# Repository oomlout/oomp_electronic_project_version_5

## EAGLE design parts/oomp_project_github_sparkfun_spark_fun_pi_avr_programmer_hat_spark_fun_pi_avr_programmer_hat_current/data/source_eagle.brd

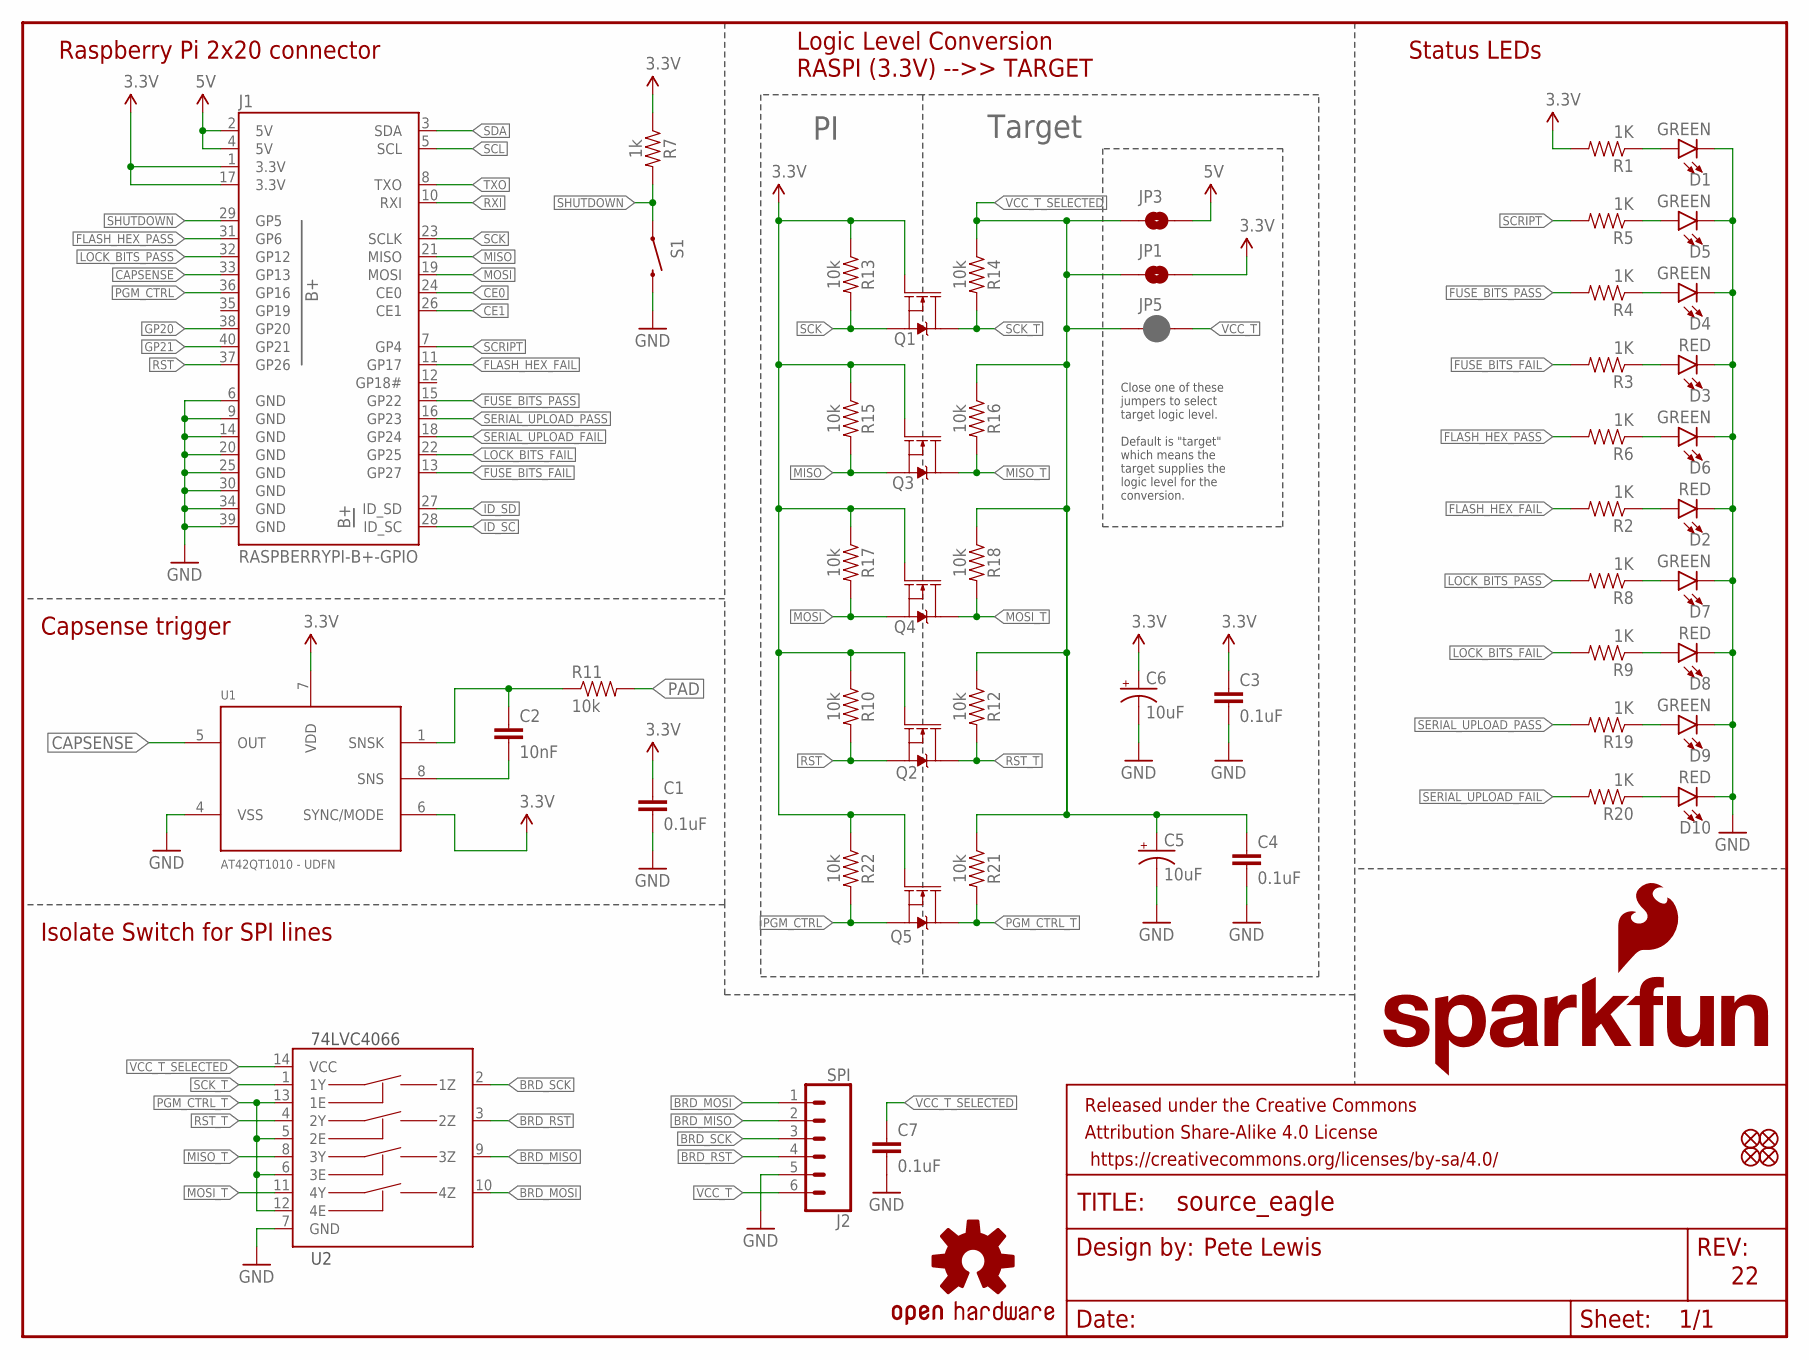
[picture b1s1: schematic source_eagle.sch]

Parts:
C1: 0.1uF; 0603-CAP
C2: 10nF; 0603-CAP
C3, C4, C7: 0.1uF; 0603
C5, C6: 10uF; EIA3216
D1, D4, D5, D6, D7, D9: GREEN; LED-1206
D2, D3, D8, D10: RED; LED-1206
FD1, FD2, FD3, FD4: FIDUCIALUFIDUCIAL; FIDUCIAL-MICRO
FRAME1: FRAME-LETTER; CREATIVE_COMMONS
J1: RASPBERRYPI-B+-GPIO; 2X20-SHROUDED
J2: SPI; 1X06-SMD_RA_MALE
JP1, JP3: JUMPER-SMT_2_NO_SILK; SMT-JUMPER_2_NO_SILK
JP5: JUMPER-SMT_2_NC_PASTE_SILK; SMT-JUMPER_2_NC_PASTE_SILK
LOGO1: SFE_LOGO_FLAME.2_INCH; SFE_LOGO_FLAME_.2
LOGO2: OSHW-LOGOL; OSHW-LOGO-L
LOGO3: SFE_LOGO_NAME.6_INCH; SFE_LOGO_NAME_.6
Q1, Q2, Q3, Q4, Q5: 220mA/50V/3.5Ω; SOT23-3
R1, R2, R3, R4, R5, R6, R8, R9, R19, R20: 1K; 0603-RES
R7: 1k; 0603
R10, R12, R13, R14, R15, R16, R17, R18, R21, R22: 10k; 0603
R11: 10k; 0603-RES
S1: SWITCH-MOMENTARY-2SMD; TACTILE-SWITCH-SMD
U1: AT42QT1010 - UDFN; UDFN/USON_8_PAD
U2: 74LVC4066; SO14

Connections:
3.3V: C1.1, C3.1, C6.+, J1.1 (3.3V), J1.17 (3.3V), JP1.2, Q1.1 (G), Q2.1 (G), Q3.1 (G), Q4.1 (G), Q5.1 (G), R1.2, R7.1, R10.1, R13.1, R15.1, R17.1, R22.1, U1.6 (SYNC/MODE), U1.7 (VDD)
5V: J1.2 (5V), J1.4 (5V), JP3.2
BRD_MISO: J2.2, U2.9 (3Z)
BRD_MOSI: J2.1, U2.10 (4Z)
BRD_RST: J2.4, U2.3 (2Z)
BRD_SCK: J2.3, U2.2 (1Z)
CAPSENSE: J1.33 (GP13), U1.5 (OUT)
CE0: J1.24 (CE0)
CE1: J1.26 (CE1)
FLASH_HEX_FAIL: J1.11 (GP17), R2.2
FLASH_HEX_PASS: J1.31 (GP6), R6.2
FUSE_BITS_FAIL: J1.13 (GP27), R3.2
FUSE_BITS_PASS: J1.15 (GP22), R4.2
GND: C1.2, C3.2, C4.2, C5.-, C6.-, C7.2, D1.C, D2.C, D3.C, D4.C, D5.C, D6.C, D7.C, D8.C, D9.C, D10.C, J1.6 (GND), J1.9 (GND), J1.14 (GND), J1.20 (GND), J1.25 (GND), J1.30 (GND), J1.34 (GND), J1.39 (GND), J2.5, S1.3 (2), U1.4 (VSS), U2.7 (GND)
GP20: J1.38 (GP20)
GP21: J1.40 (GP21)
ID_SC: J1.28 (ID_SC)
ID_SD: J1.27 (ID_SD)
LOCK_BITS_FAIL: J1.22 (GP25), R9.2
LOCK_BITS_PASS: J1.32 (GP12), R8.2
MISO: J1.21 (MISO), Q3.2 (S), R15.2
MISO_T: Q3.3 (D), R16.2, U2.8 (3Y)
MOSI: J1.19 (MOSI), Q4.2 (S), R17.2
MOSI_T: Q4.3 (D), R18.2, U2.11 (4Y)
unnamed: D6.A, R6.1
unnamed: D1.A, R1.1
unnamed: D2.A, R2.1
unnamed: D3.A, R3.1
unnamed: D7.A, R8.1
unnamed: D4.A, R4.1
unnamed: D5.A, R5.1
unnamed: D8.A, R9.1
unnamed: C2.2, U1.8 (SNS)
unnamed: C2.1, R11.1, U1.1 (SNSK)
unnamed: D9.A, R19.1
unnamed: D10.A, R20.1
PAD: R11.2
PGM_CTRL: J1.36 (GP16), Q5.2 (S), R22.2
PGM_CTRL_T: Q5.3 (D), R21.2, U2.5 (2E), U2.6 (3E), U2.12 (4E), U2.13 (1E)
RST: J1.37 (GP26), Q2.2 (S), R10.2
RST_T: Q2.3 (D), R12.2, U2.4 (2Y)
RXI: J1.10 (RXI)
SCK: J1.23 (SCLK), Q1.2 (S), R13.2
SCK_T: Q1.3 (D), R14.2, U2.1 (1Y)
SCL: J1.5 (SCL)
SCRIPT: J1.7 (GP4), R5.2
SDA: J1.3 (SDA)
SERIAL_UPLOAD_FAIL: J1.18 (GP24), R20.2
SERIAL_UPLOAD_PASS: J1.16 (GP23), R19.2
SHUTDOWN: J1.29 (GP5), R7.2, S1.1
TXO: J1.8 (TXO)
VCC_T: J2.6, JP5.2
VCC_T_SELECTED: C4.1, C5.+, C7.1, JP1.1, JP3.1, JP5.1, R12.1, R14.1, R16.1, R18.1, R21.1, U2.14 (VCC)

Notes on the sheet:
Raspberry Pi 2x20 connector
Pete Lewis
Status LEDs
Capsense trigger
Target
Logic Level Conversion RASPI (3.3V) -->> TARGET
Isolate Switch for SPI lines
Close one of these jumpers to select target logic level. Default is "target" which means the target supplies the logic level for the conversion.

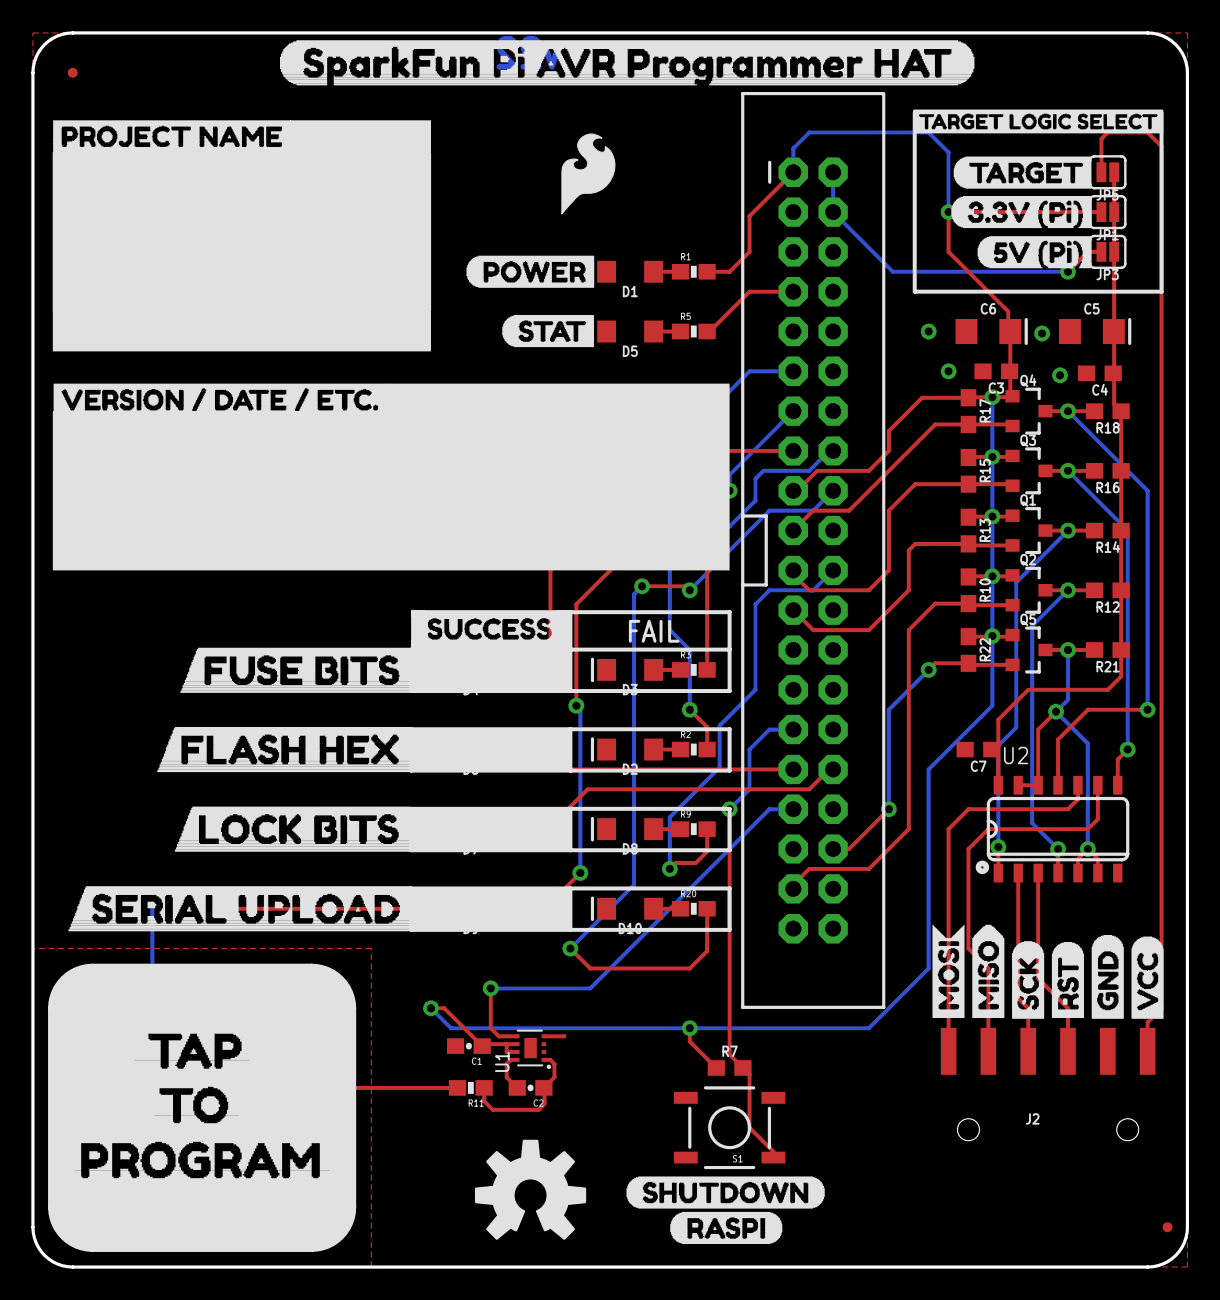
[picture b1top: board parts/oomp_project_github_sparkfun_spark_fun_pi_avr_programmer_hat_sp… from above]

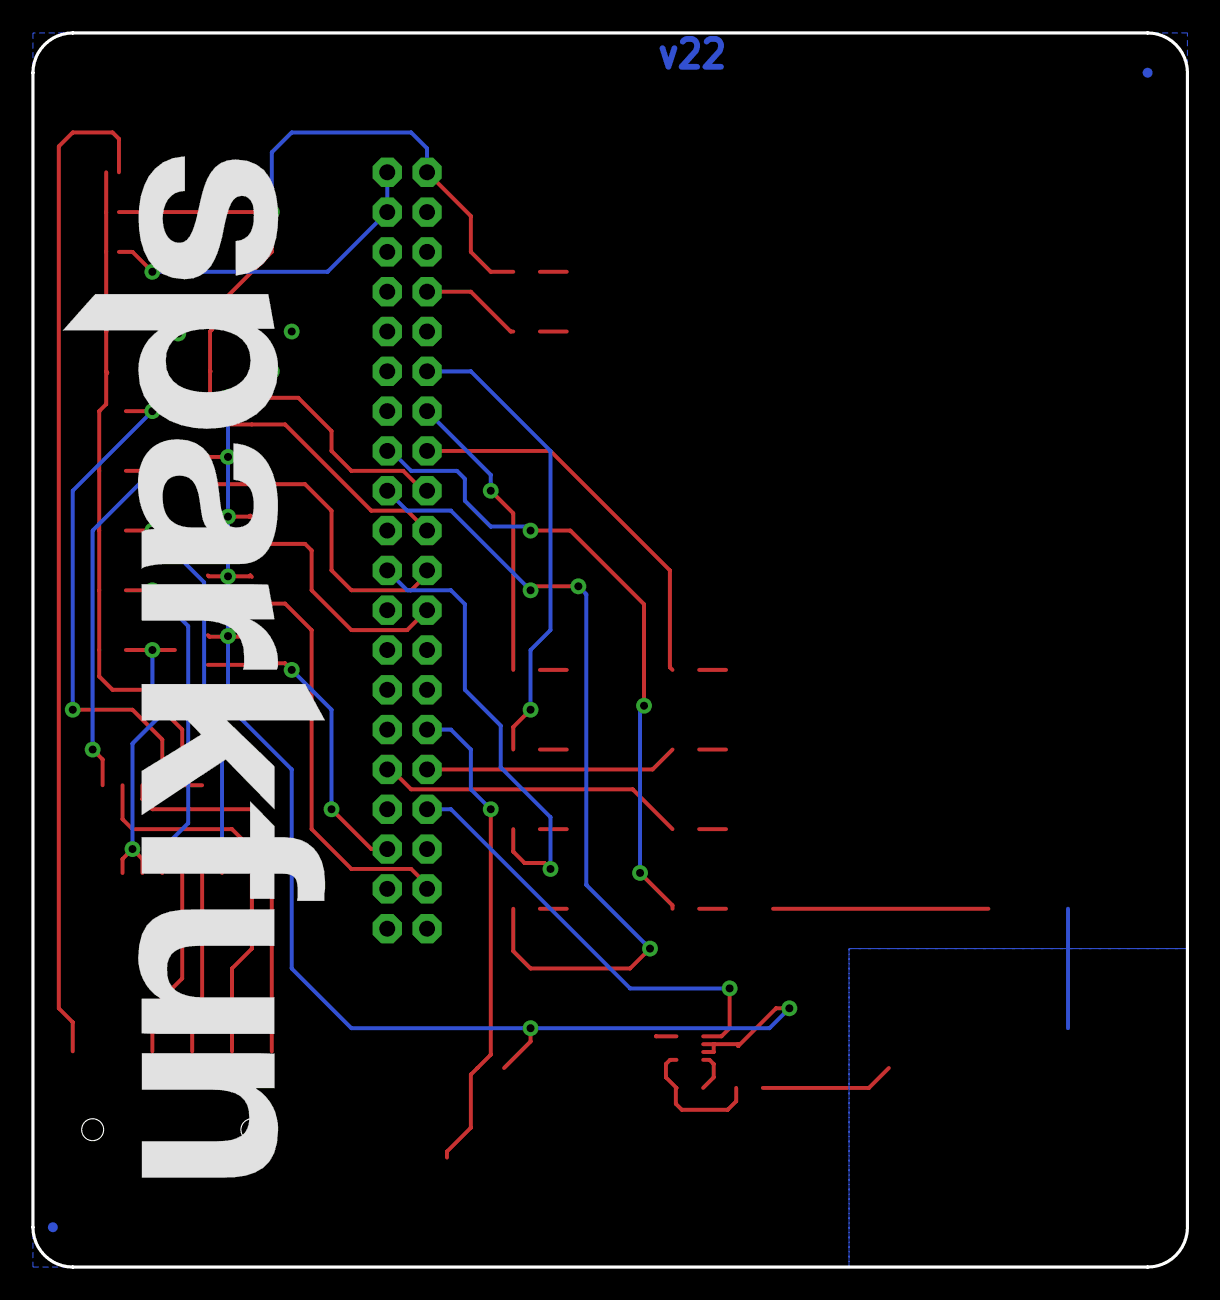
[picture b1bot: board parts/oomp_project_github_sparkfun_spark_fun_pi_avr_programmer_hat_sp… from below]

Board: 2 copper layers, 73.7 x 78.7 mm, 85 parts (3 on the bottom side), 42 nets.

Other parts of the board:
U$1: SPARKFUN_PI_AVR_PROGRAMMER_HAT0
U$2: PROJECT_NAME0
U$3: VERSION_#_DATE_#_ETC#0
U$4: TARGET_LOGIC_SELECT4
U$5: POWER0
U$6: STAT1
U$7: SHUTDOWN2
U$8: RASPI3
U$9: 3#3V_#PI#7
U$10: 5V_#PI#8
U$11: TARGET0
U$12: MISO1
U$13: MOSI0
U$14: SCK2
U$15: RST3
U$16: GND4
U$18: TAP0
U$19: TO1
U$20: PROGRAM2
U$21: VCC0
U$22: SUCCESS0
U$23: FUSE_BITS2
U$24: FLASH_HEX3
U$25: LOCK_BITS4
U$26: SERIAL_UPLOAD5

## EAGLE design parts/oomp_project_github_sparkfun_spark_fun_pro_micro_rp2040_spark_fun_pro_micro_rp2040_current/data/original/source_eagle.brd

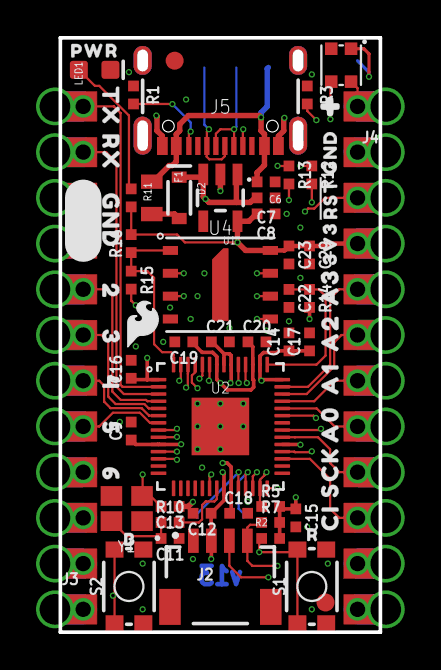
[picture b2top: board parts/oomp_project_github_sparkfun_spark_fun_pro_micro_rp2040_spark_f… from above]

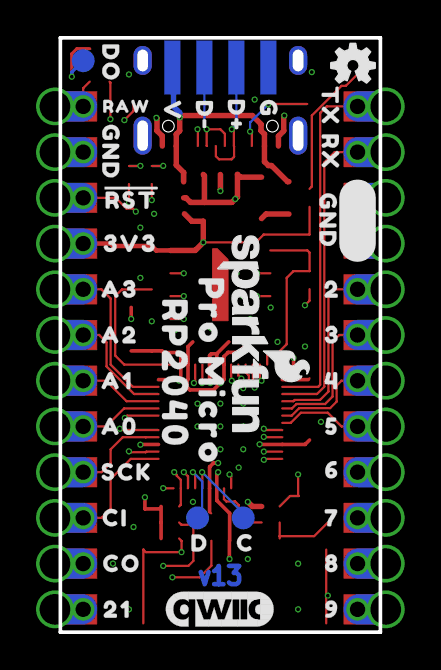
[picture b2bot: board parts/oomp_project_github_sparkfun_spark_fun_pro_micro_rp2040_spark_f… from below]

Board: 4 copper layers, 17.8 x 33.0 mm, 109 parts (39 on the bottom side), 49 nets.

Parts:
C6: 1.0uF; 0402-TIGHT
C7, C8: 10uF; 0402-TIGHT
C9, C12, C14, C15, C16, C17, C18, C19, C29: 0.1uF; 0402-TIGHT
C11, C13: 15pF; 0402-TIGHT
C20, C21, C22, C23: 2.2uF; 0402-TIGHT
D2: 3A/10V/280mV; SOD-323
F1: 6V 0.5A; 0805
FRAME2: FRAME-LEDGER; CREATIVE_COMMONS
J2: Qwiic; JST04_1MM_RA
J3, J4: 1X12_CASTELLATED
J5: USB Female Type C Connector; USB-C-16P_4LAYER-PADS
JP1, JP2: FIDUCIAL1X2; FIDUCIAL-1X2
JP14: USB_SOLDER_PADS; USB-SOLDER-PADS
LED1: RED; LED-0603
LOGO1: SFE_LOGO_NAME_FLAME.1_INCH; SFE_LOGO_NAME_FLAME_.1
LOGO3: QWIIC_LOGO_6MM; QWIIC_6MM
LOGO4: SFE_LOGO_FLAME.1_INCH; SFE_LOGO_FLAME_.1
LOGO5: SPECIAL_INSTRUCTIONS-ORDERING; ORDERING_INSTRUCTIONS
R1, R3: 5.1k; 0402-TIGHT
R2, R16: 10k; 0402-TIGHT
R5, R7: 2.2k; 0402-TIGHT
R10, R11, R15: 1k; 0402-TIGHT
R12, R13: 27; 0402-TIGHT
R14: 200; 0402-TIGHT
S1: Reset; TACTILE_SWITCH_SMD_4.6X2.8MM
S2: Boot; TACTILE_SWITCH_SMD_4.6X2.8MM
TP1, TP2, TP3: PAD.03X.05
U1: 3.3V; SOT23-5
U2: RP2040; QFN-56
U3: WS2812-2020
U4: W25QXX128MBIT; WSON-8-6X5-SKINNY_CENTERPAD
U$1, U$11: A00
U$2: GND_0
U$3: OSHW-LOGOMINI; OSHW-LOGO-MINI
U$4: PRO_MICRO0
U$5: #0
U$6: 70
U$7: 81
U$8: 92
U$9, U$64: CI4
U$10, U$67: SCK3
U$12, U$20: A10
U$13, U$33: A21
U$14, U$39: A32
U$15, U$22, U$74: GND2
U$16: 3V3_0
U$17: RAW0
U$18: C0
U$19, U$76: TX0
U$21, U$75: RX1
U$23, U$53: 20
U$24, U$54: 31
U$25, U$55: 42
U$26, U$56: 53
U$27, U$57: 64
U$28: D#1
U$29: D#2
U$30: G0
U$31: V3
U$32: 210
U$34: #RST#0
U$35: D1
U$36: B0
U$37: R0
U$38: RP20401
U$40: DO0
U$66: CO5
U$68: #RST#1
U$69: 3V30
U$73: PWR0
Y1: 12MHz; CRYSTAL-SMD-2X2.5MM

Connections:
0/TX0: J3.12, J3.12B, U2.2
1.1V: C18.1, C19.1, C20.1, U2.23, U2.45, U2.50
1/RX0: J3.11, J3.11B, U2.3
2: J3.8, J3.8B, U2.4
3: J3.7, J3.7B, U2.5
3.3V: C8.2, C9.1, C12.1, C14.1, C15.1, C16.1, C17.1, C21.1, C23.1, C29.1, J2.2, J4.4, J4.4B, R2.2, R5.2, R7.2, R11.2, R14.2, R16.2, U1.5, U2.1, U2.10, U2.22, U2.33, U2.42, U2.44, U2.48, U2.49, U4.8
4: J3.6, J3.6B, U2.6
5: J3.5, J3.5B, U2.7
6: J3.4, J3.4B, U2.8
7: J3.3, J3.3B, U2.9
8/TX1: J3.2, J3.2B, U2.11
9/RX1: J3.1, J3.1B, U2.12
16/SDA: J2.3, R5.1, U2.27
17/SCL: J2.4, R7.1, U2.28
20/SPI_CIPO: J4.10, J4.10B, U2.31
21/SPI_!CS!: J4.12, J4.12B, U2.32
22/SPI_SCK: J4.9, J4.9B, U2.34
23/SPI_COPI: J4.11, J4.11B, U2.35
25/WS2812-DI: U2.37, U3.3
!RESET!: J4.3, J4.3B, R2.1, S1.3, S1.4, U2.26
A0: J4.8, J4.8B, U2.38
A1: J4.7, J4.7B, U2.39
A2: J4.6, J4.6B, U2.40
A3: J4.5, J4.5B, U2.41
ADC_VDD: C22.1, R14.1, U2.43
BOOT: R15.2, S2.3, S2.4
GND: C6.1, C7.1, C8.1, C9.2, C11.1, C12.2, C13.1, C14.2, C15.2, C16.2, C17.2, C18.2, C19.2, C20.2, C21.2, C22.2, C23.2, C29.2, J2.1, J3.9, J3.9B, J3.10, J3.10B, J4.2, J4.2B, J5.GND, J5.GND2, JP14.GND, LED1.C, R1.1, R3.1, S1.1, S1.2, S2.1, S2.2, U1.2, U2.19, U2.EPAD, U3.2, U4.4
unnamed: TP3.P$1, U3.1
unnamed: J5.A5, R3.2
unnamed: J5.B5, R1.2
unnamed: LED1.A, R11.1
QSPI-0: U2.53, U4.5
QSPI-1: U2.55, U4.2
QSPI-2: U2.54, U4.3
QSPI-3: U2.51, U4.7
QSPI-CLK: U2.52, U4.6
QSPI-CS: R15.1, R16.1, U2.56, U4.1
RAW: C7.2, D2.C, J4.1, J4.1B, U1.1, U1.3, U3.4
RP_D1+: R13.2, U2.47
RP_D1-: R12.2, U2.46
RP_D+: J5.A6, J5.B6, JP14.D+, R13.1
RP_D-: J5.A7, J5.B7, JP14.D-, R12.1
SWDCK: TP1.P$1, U2.24
SWDIO: TP2.P$1, U2.25
USB_RAW: D2.A, F1.2
V_USB: C6.2, F1.1, J5.VBUS1, J5.VBUS2, JP14.VBUS
X1A: R10.2, U2.21
X1B: C11.2, R10.1, Y1.P1
X2: C13.2, U2.20, Y1.P3

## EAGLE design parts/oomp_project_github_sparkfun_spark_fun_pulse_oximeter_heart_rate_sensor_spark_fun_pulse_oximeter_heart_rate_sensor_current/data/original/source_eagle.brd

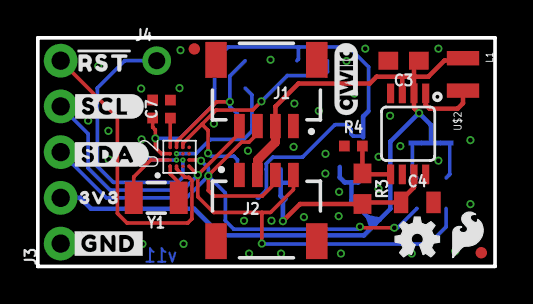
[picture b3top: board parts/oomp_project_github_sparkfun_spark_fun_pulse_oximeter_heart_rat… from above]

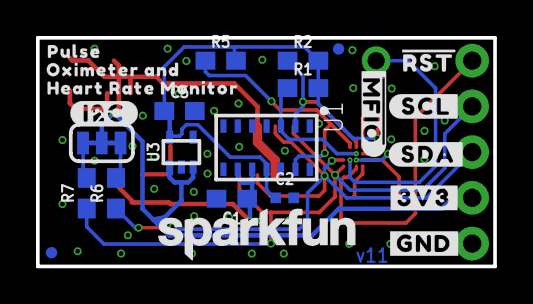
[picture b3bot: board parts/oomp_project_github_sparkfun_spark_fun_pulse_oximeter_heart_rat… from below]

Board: 2 copper layers, 25.4 x 12.7 mm, 50 parts (24 on the bottom side), 18 nets.

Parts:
C1, C3: 10uF; 0603
C2: 0.1uF; 0402-TIGHT
C4: 22uF; 0805
C5: 1.0uF; 0603
C6, C7: 1.0uF; 0402-TIGHT
FD1, FD2, FD3, FD4: FIDUCIALUFIDUCIAL; FIDUCIAL-MICRO
FRAME1: FRAME-LETTER; CREATIVE_COMMONS
I2C: JUMPER-SMT_3_2-NC_TRACE_SILK; SMT-JUMPER_3_2-NC_TRACE_SILK
J1, J2: QWIIC_RIGHT_ANGLE; JST04_1MM_RA
J3: 1X05_NO_SILK
J4: 1X01_NO_SILK
L1: 2.2μH; 0806
LOGO1: SFE_LOGO_FLAME.1_INCH; SFE_LOGO_FLAME_.1
LOGO2: OSHW-LOGOMINI; OSHW-LOGO-MINI
LOGO3: SFE_LOGO_NAME.1_INCH; SFE_LOGO_NAME_.1
LOGO4: SPECIAL_INSTRUCTIONS-ORDERING; ORDERING_INSTRUCTIONS
LOGO5: QWIIC_LOGO_4MM; QWIIC_4MM
R1, R2, R5, R6, R7: 4.7k; 0603
R3: 750K; 0603
R4: 100k; 0402-TIGHT
U1: MAX30101EFD; 14_PIN_OESIP
U2: MAX32664GWEA; 16_PIN_WLP
U3: 1.8V/100mA; SC70
U$1: #I2C#1348
U$2: PAM2401; MSOP8
U$3, U$5: #GND#0
U$4: #SCL#7
U$6, U$12: #RST#32
U$7: 3V338
U$8: #SDA#10
U$9: #3V3#1
U$10: #SDA#9
U$11: #SCL#9
U$13: ##MFIO##12
U$17: PULSE35
U$20: OXIMETER_AND36
U$21: HEART_RATE_MONITOR37
Y1: 32.768kHz; CRYSTAL-SMD-3.2X1.5MM

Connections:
1.8V: C2.1, C5.1, C6.1, R1.2, R2.2, R5.2, U1.P11, U2.3, U3.5
3.3V: C3.1, I2C.2, J1.2, J2.2, J3.2, L1.1, U3.1, U3.3, U$2.2, U$2.3
5V: C1.1, C4.1, R3.2, U1.P9, U1.P10, U$2.7
!HR_INT: R5.1, U1.P13, U2.6
!MFIO: J4.1, U2.16
!RST: J3.5, U2.12
GND: C1.2, C2.2, C3.2, C4.2, C5.2, C6.2, C7.2, J1.1, J2.1, J3.1, R4.1, U1.P4, U1.P12, U2.13, U3.2, U$2.4, U$2.8
HOST_SCL: J1.4, J2.4, J3.4, R7.1, U2.10
HOST_SDA: J1.3, J2.3, J3.3, R6.1, U2.9
unnamed: C7.1, U2.4
unnamed: R3.1, R4.2, U$2.5
unnamed: L1.2, U$2.1
unnamed: I2C.3, R6.2
unnamed: I2C.1, R7.2
unnamed: U2.1, Y1.P$1
unnamed: U2.2, Y1.P$2
SNSR_SCL: R2.1, U1.P2, U2.5
SNSR_SDA: R1.1, U1.P3, U2.14

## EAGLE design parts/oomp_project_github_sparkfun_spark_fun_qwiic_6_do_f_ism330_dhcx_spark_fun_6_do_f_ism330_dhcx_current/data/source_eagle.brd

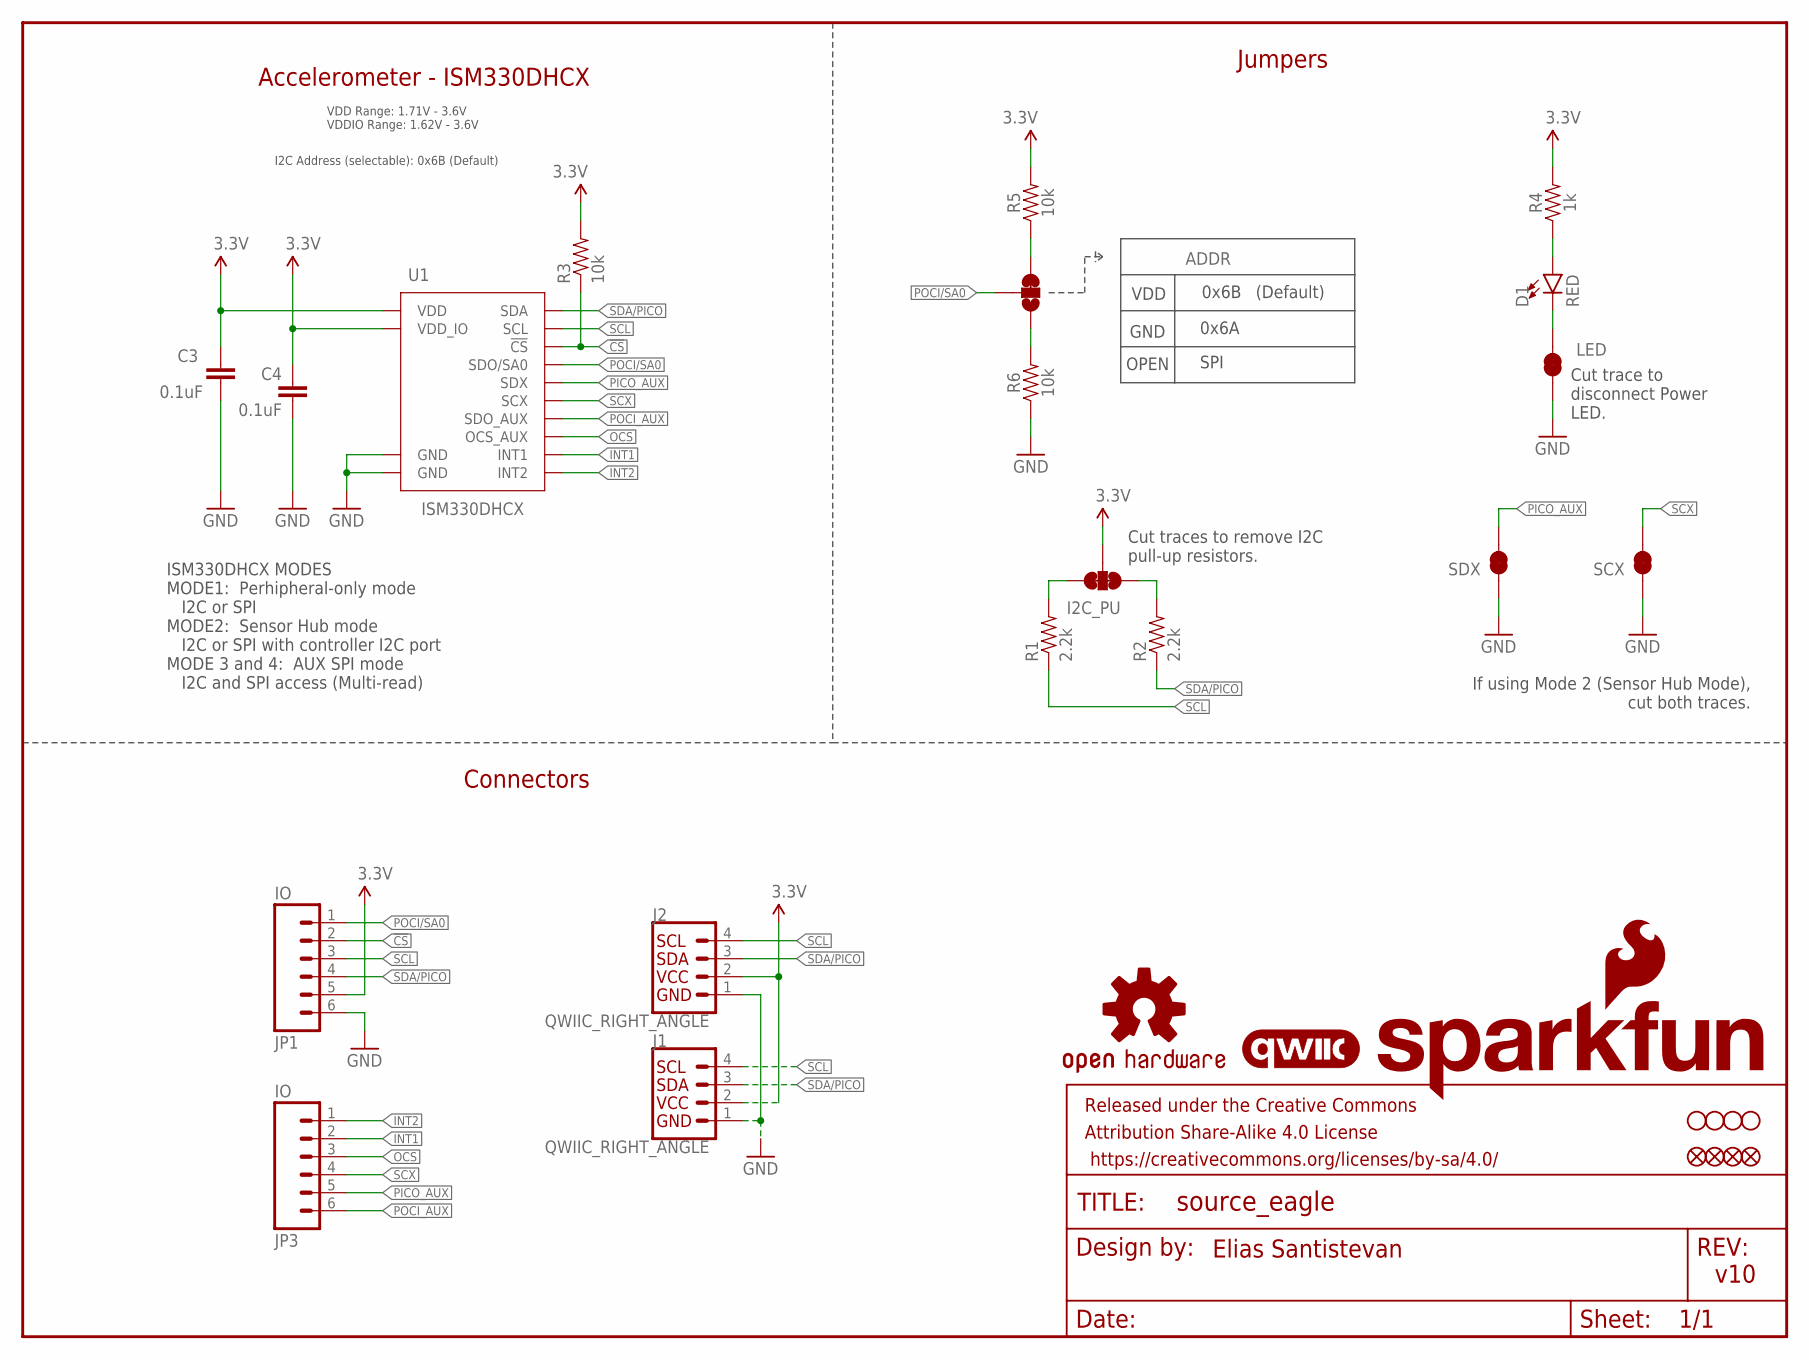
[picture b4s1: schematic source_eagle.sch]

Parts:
ADDR: JUMPER-SMT_3_1-NC_TRACE_SILK; SMT-JUMPER_3_1-NC_TRACE_SILK
C3, C4: 0.1uF; 0603
D1: RED; LED-0603
FD1, FD2: FIDUCIALUFIDUCIAL; FIDUCIAL-MICRO
FID1, FID2: FIDUCIALUFIDUCIAL; FIDUCIAL-MICRO
FRAME1: FRAME-LETTER; CREATIVE_COMMONS
I2C_PU: S_MODE; SMT-JUMPER_3_2-NC_TRACE_SILK
J1, J2: QWIIC_RIGHT_ANGLE; JST04_1MM_RA
JP1, JP3: IO; 1X06_NO_SILK
LED: JUMPER-SMT_2_NC_TRACE_SILK; SMT-JUMPER_2_NC_TRACE_SILK
LOGO1: QWIIC_LOGO_4MM; QWIIC_4MM
LOGO2: OSHW-LOGOMINI; OSHW-LOGO-MINI
LOGO3: SFE_LOGO_NAME_FLAME.1_INCH; SFE_LOGO_NAME_FLAME_.1
R1, R2: 2.2k; 0603
R3, R5, R6: 10k; 0603
R4: 1k; 0603
SCX: JUMPER-SMT_2_NC_TRACE_SILK; SMT-JUMPER_2_NC_TRACE_SILK
SDX: JUMPER-SMT_2_NC_TRACE_SILK; SMT-JUMPER_2_NC_TRACE_SILK
STANDOFF1, STANDOFF2, STANDOFF3, STANDOFF4: STAND-OFFTIGHT; STAND-OFF-TIGHT
U1: ISM330DHCX; LGA-14L

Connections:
3.3V: C3.1, C4.1, I2C_PU.2, J1.2, J2.2, JP1.5, R3.2, R4.2, R5.2, U1.P5 (VDD_IO), U1.P8 (VDD)
!CS!: JP1.2, R3.1, U1.P12 (!CS!)
GND: C3.2, C4.2, J1.1, J2.1, JP1.6, LED.1, R6.1, SCX.1, SDX.1, U1.P6 (GND), U1.P7 (GND)
INT1: JP3.2, U1.P4 (INT1)
INT2: JP3.1, U1.P9 (INT2)
unnamed: ADDR.3, R5.1
unnamed: D1.A, R4.1
unnamed: D1.C, LED.2
unnamed: I2C_PU.1, R1.2
unnamed: I2C_PU.3, R2.2
unnamed: ADDR.1, R6.2
OCS: JP3.3, U1.P10 (OCS_AUX)
PICO_AUX: JP3.5, SDX.2, U1.P2 (SDX)
POCI/SA0: ADDR.2, JP1.1, U1.P1 (SDO/SA0)
POCI_AUX: JP3.6, U1.P11 (SDO_AUX)
SCL: J1.4, J2.4, JP1.3, R1.1, U1.P13 (SCL)
SCX: JP3.4, SCX.2, U1.P3 (SCX)
SDA/PICO: J1.3, J2.3, JP1.4, R2.1, U1.P14 (SDA)

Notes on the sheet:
Accelerometer - ISM330DHCX
If using Mode 2 (Sensor Hub Mode), cut both traces.
Cut traces to remove I2C pull-up resistors.
ISM330DHCX MODES MODE1: Perhipheral-only mode I2C or SPI MODE2: Sensor Hub mode I2C or SPI with controller I2C port MODE 3 and 4: AUX SPI mode I2C and SPI access (Multi-read)
VDD Range: 1.71V - 3.6V VDDIO Range: 1.62V - 3.6V
v10
Jumpers
Cut trace to disconnect Power LED.
Connectors
VDD
GND
OPEN
0x6B
0x6A
SPI
Elias Santistevan
(Default)
I2C Address (selectable): 0x6B (Default)

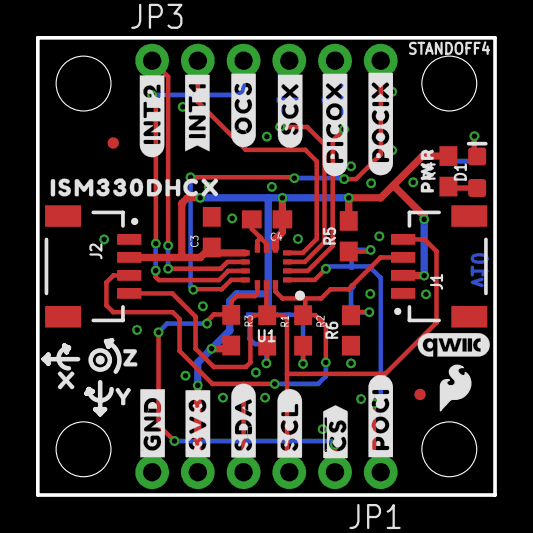
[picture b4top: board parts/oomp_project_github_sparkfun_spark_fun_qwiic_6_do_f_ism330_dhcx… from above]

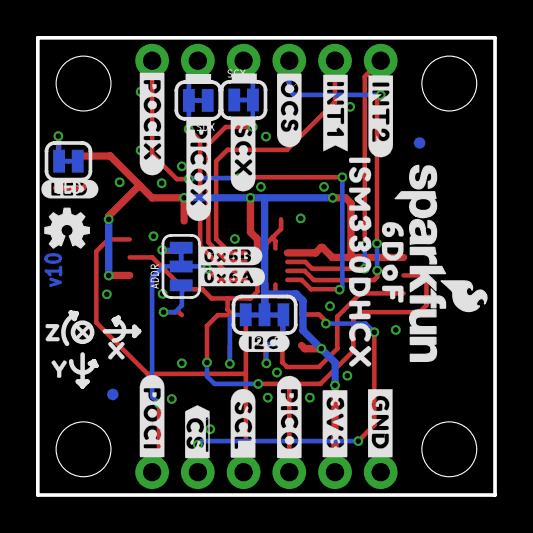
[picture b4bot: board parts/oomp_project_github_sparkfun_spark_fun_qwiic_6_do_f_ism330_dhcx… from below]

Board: 2 copper layers, 25.4 x 25.4 mm, 70 parts (30 on the bottom side), 18 nets.

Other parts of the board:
U$1, U$15: #3V3#1
U$2, U$17: #GND#0
U$3: ##CS##7
U$4: #SDA#4
U$5, U$22: #SCL#5
U$6: #POCI#11
U$7, U$19: #INT1#9
U$8: #INT2#2
U$9: #OCS#8
U$10: #SCX#9
U$11: #PICOX#10
U$12: ISM330DHCX331
U$13: #0X6A#11
U$14: #0X6B#11
U$16: #LED#11
U$18: #POCI#12
U$20: #OCS#7
U$23: #SCX#8
U$24: #POCIX#8
U$25: #I2C#11
U$26: #PICO#13
U$27: ##CS##8
U$28: PWR8
U$29: SFE_LOGO_FLAME_.1
U$30: ISM330DHCX20
U$31: 6DOF12
U$32: #PICOX#9
U$33: #POCIX#7
U$34, U$37: X2114
U$35, U$38: Y2115
U$36, U$39: Z2116
U$40: #INT2#3

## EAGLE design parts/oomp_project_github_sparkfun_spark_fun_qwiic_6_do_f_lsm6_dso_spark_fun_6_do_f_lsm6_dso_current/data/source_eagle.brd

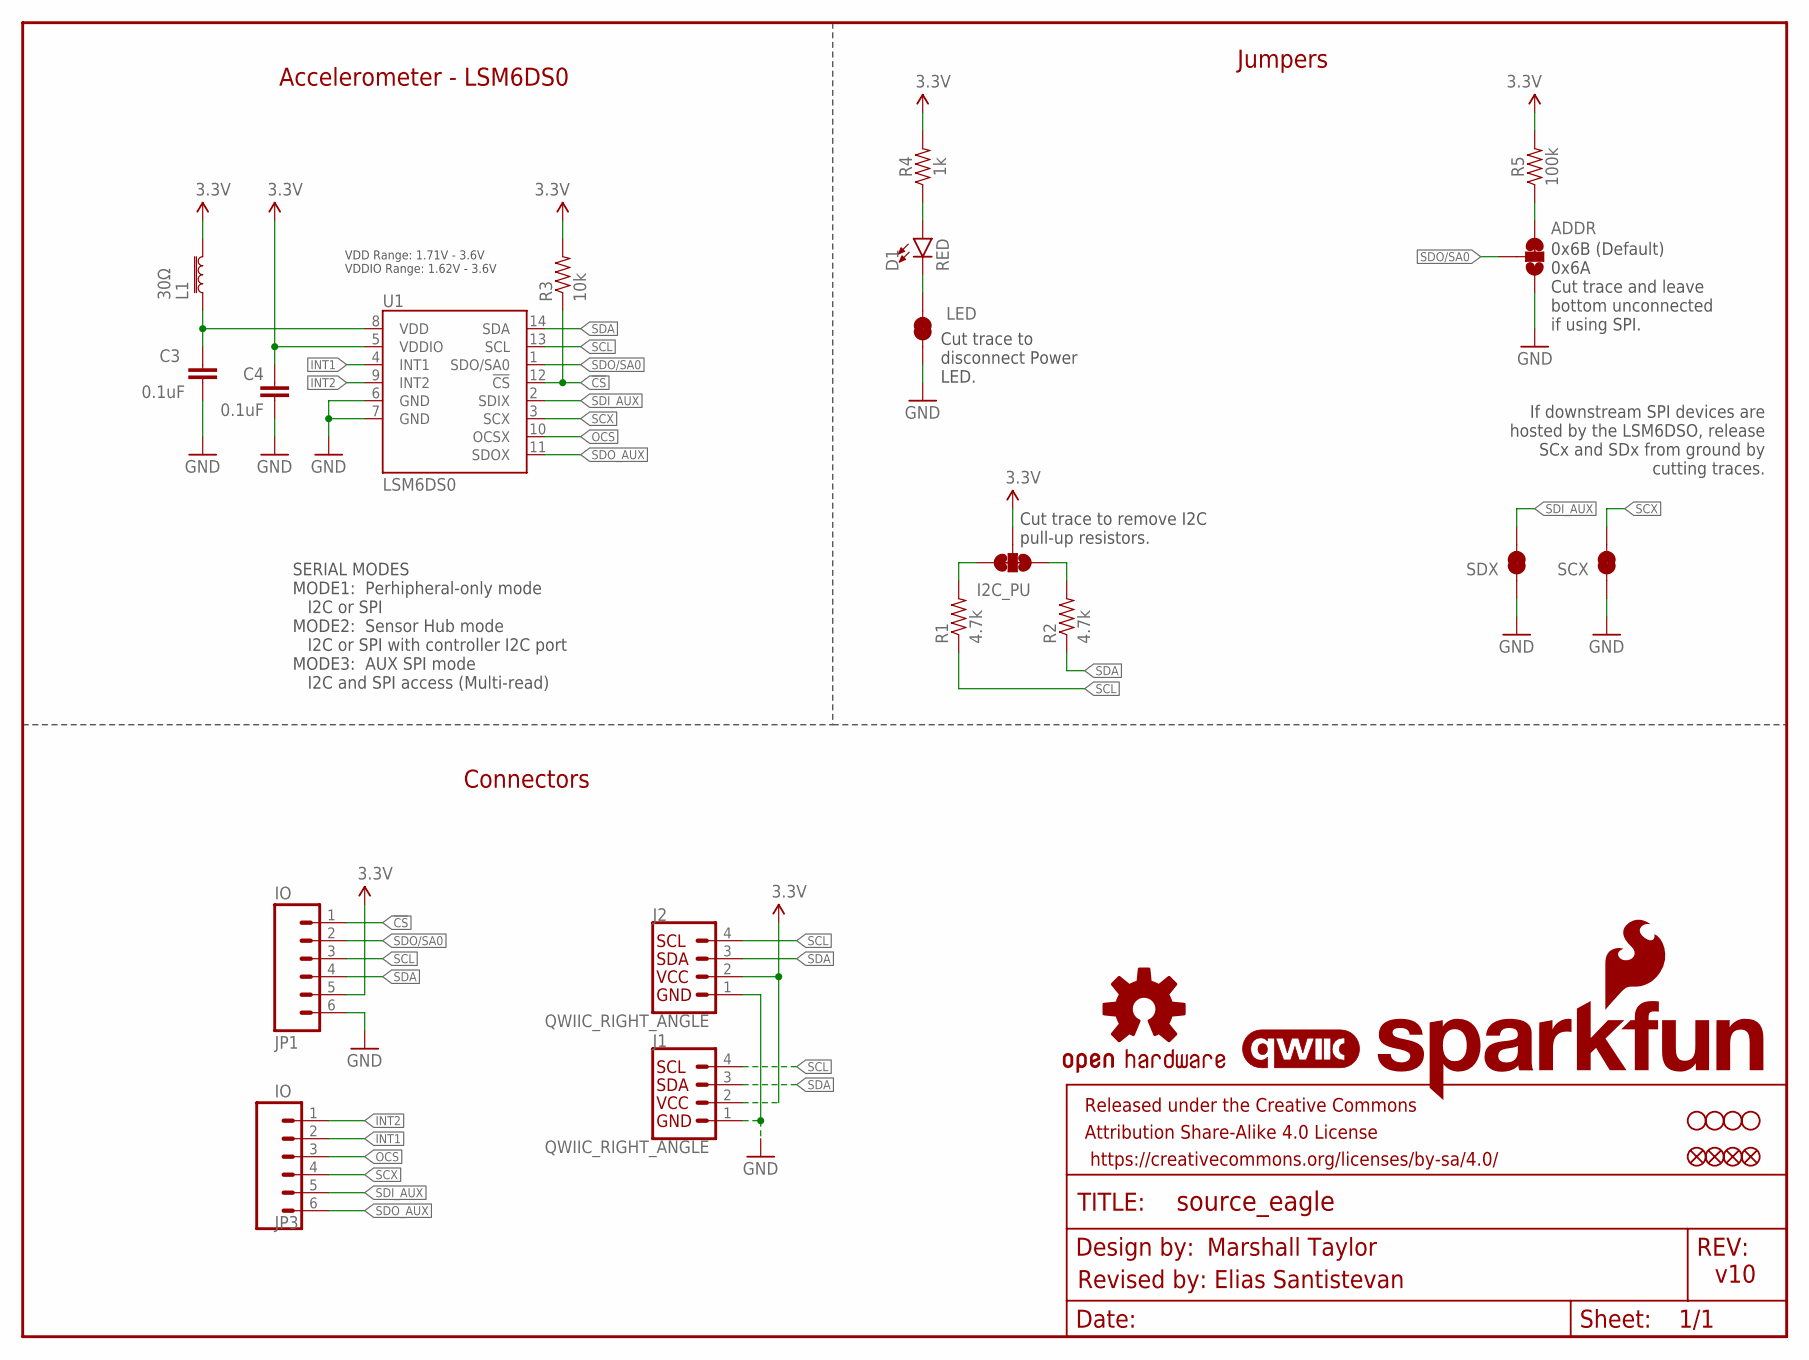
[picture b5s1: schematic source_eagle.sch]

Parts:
ADDR: JUMPER-SMT_3_1-NC_TRACE_SILK; SMT-JUMPER_3_1-NC_TRACE_SILK
C3, C4: 0.1uF; 0603
D1: RED; LED-0603
FD1, FD2: FIDUCIALUFIDUCIAL; FIDUCIAL-MICRO
FID1, FID2: FIDUCIALUFIDUCIAL; FIDUCIAL-MICRO
FRAME1: FRAME-LETTER; CREATIVE_COMMONS
I2C_PU: S_MODE; SMT-JUMPER_3_2-NC_TRACE_SILK
J1, J2: QWIIC_RIGHT_ANGLE; JST04_1MM_RA
JP1, JP3: IO; 1X06_NO_SILK
L1: 30Ω; 0603
LED: JUMPER-SMT_2_NC_TRACE_SILK; SMT-JUMPER_2_NC_TRACE_SILK
LOGO1: QWIIC_LOGO_4MM; QWIIC_4MM
LOGO2: OSHW-LOGOS; OSHW-LOGO-S
LOGO3: SFE_LOGO_NAME_FLAME.1_INCH; SFE_LOGO_NAME_FLAME_.1
R1, R2: 4.7k; 0603
R3: 10k; 0603
R4: 1k; 0603
R5: 100k; 0603
SCX: JUMPER-SMT_2_NC_TRACE_SILK; SMT-JUMPER_2_NC_TRACE_SILK
SDX: JUMPER-SMT_2_NC_TRACE_SILK; SMT-JUMPER_2_NC_TRACE_SILK
STANDOFF1, STANDOFF2, STANDOFF3, STANDOFF4: STAND-OFFTIGHT; STAND-OFF-TIGHT
U1: LSM6DS0; LGA14L

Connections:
3.3V: C4.1, I2C_PU.2, J1.2, J2.2, JP1.5, L1.1, R3.2, R4.2, R5.2, U1.5 (VDDIO)
!CS!: JP1.1, R3.1, U1.12 (!CS!)
GND: ADDR.1, C3.2, C4.2, J1.1, J2.1, JP1.6, LED.1, SCX.1, SDX.1, U1.6 (GND), U1.7 (GND)
INT1: JP3.2, U1.4 (INT1)
INT2: JP3.1, U1.9 (INT2)
unnamed: ADDR.3, R5.1
unnamed: D1.A, R4.1
unnamed: D1.C, LED.2
unnamed: I2C_PU.1, R1.2
unnamed: I2C_PU.3, R2.2
OCS: JP3.3, U1.10 (OCSX)
SCL: J1.4, J2.4, JP1.3, R1.1, U1.13 (SCL)
SCX: JP3.4, SCX.2, U1.3 (SCX)
SDA: J1.3, J2.3, JP1.4, R2.1, U1.14 (SDA)
SDI_AUX: JP3.5, SDX.2, U1.2 (SDIX)
SDO/SA0: ADDR.2, JP1.2, U1.1 (SDO/SA0)
SDO_AUX: JP3.6, U1.11 (SDOX)
VDD: C3.1, L1.2, U1.8 (VDD)

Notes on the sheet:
Accelerometer - LSM6DS0
If downstream SPI devices are hosted by the LSM6DSO, release SCx and SDx from ground by cutting traces.
Cut trace to remove I2C pull-up resistors.
SERIAL MODES MODE1: Perhipheral-only mode I2C or SPI MODE2: Sensor Hub mode I2C or SPI with controller I2C port MODE3: AUX SPI mode I2C and SPI access (Multi-read)
Revised by: Elias Santistevan
VDD Range: 1.71V - 3.6V VDDIO Range: 1.62V - 3.6V
v10
0x6B (Default) 0x6A Cut trace and leave bottom unconnected if using SPI.
Jumpers
Cut trace to disconnect Power LED.
Connectors

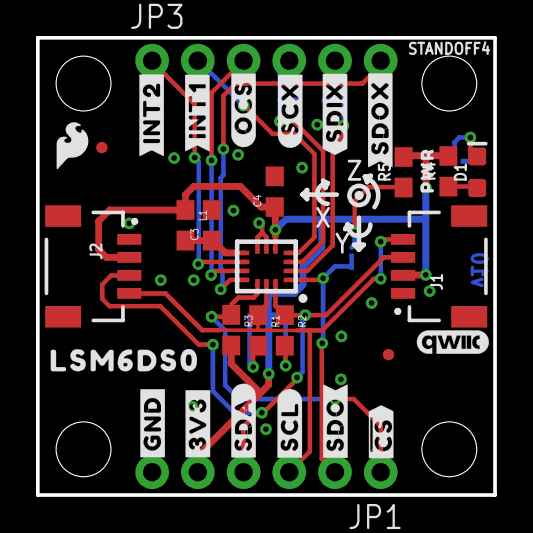
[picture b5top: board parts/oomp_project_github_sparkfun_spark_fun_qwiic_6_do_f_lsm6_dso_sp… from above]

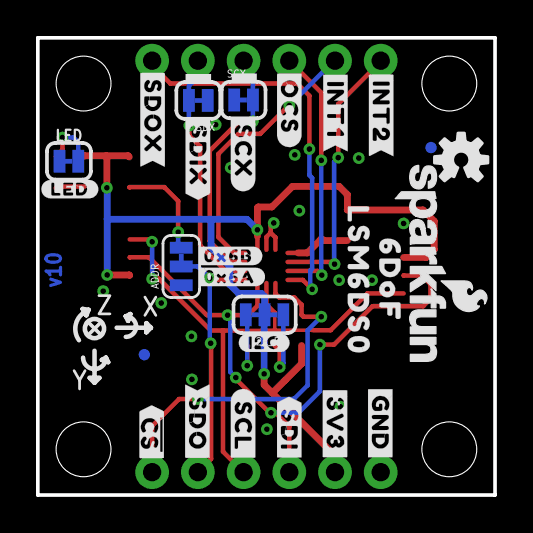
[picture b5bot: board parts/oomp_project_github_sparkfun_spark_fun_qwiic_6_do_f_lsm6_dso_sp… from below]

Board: 2 copper layers, 25.4 x 25.4 mm, 64 parts (27 on the bottom side), 18 nets.

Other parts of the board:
U$1, U$15: #3V3#1
U$2, U$17: #GND#0
U$3: ##CS##7
U$4: #SDA#4
U$5, U$22: #SCL#5
U$6: #SDO#6
U$7, U$19: #INT1#9
U$8, U$21: #INT2#9
U$9: #OCS#8
U$10: #SCX#9
U$11, U$33: #SDIX#11
U$12, U$30: LSM6DS011
U$13: #0X6A#11
U$14: #0X6B#11
U$16: #LED#11
U$18: #SDO#7
U$20: #OCS#7
U$23: #SCX#8
U$24, U$32: #SDOX#12
U$25: #I2C#11
U$26: #SDI#4
U$27: ##CS##8
U$28: PWR8
U$29: SFE_LOGO_FLAME_.1
U$31: 6DOF12

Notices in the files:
parts and their libraries:
SparkFun-Boards: Licensing: CC v3.0 Share-Alike You are welcome to use this library for commercial purposes.
SparkFun-LED: Licensing: Creative Commons ShareAlike 4.0 International - https://creativecommons.org/licenses/by-sa/4.0
SparkFun-Aesthetics: https://creativecommons.org/licenses/by-sa/4.0
